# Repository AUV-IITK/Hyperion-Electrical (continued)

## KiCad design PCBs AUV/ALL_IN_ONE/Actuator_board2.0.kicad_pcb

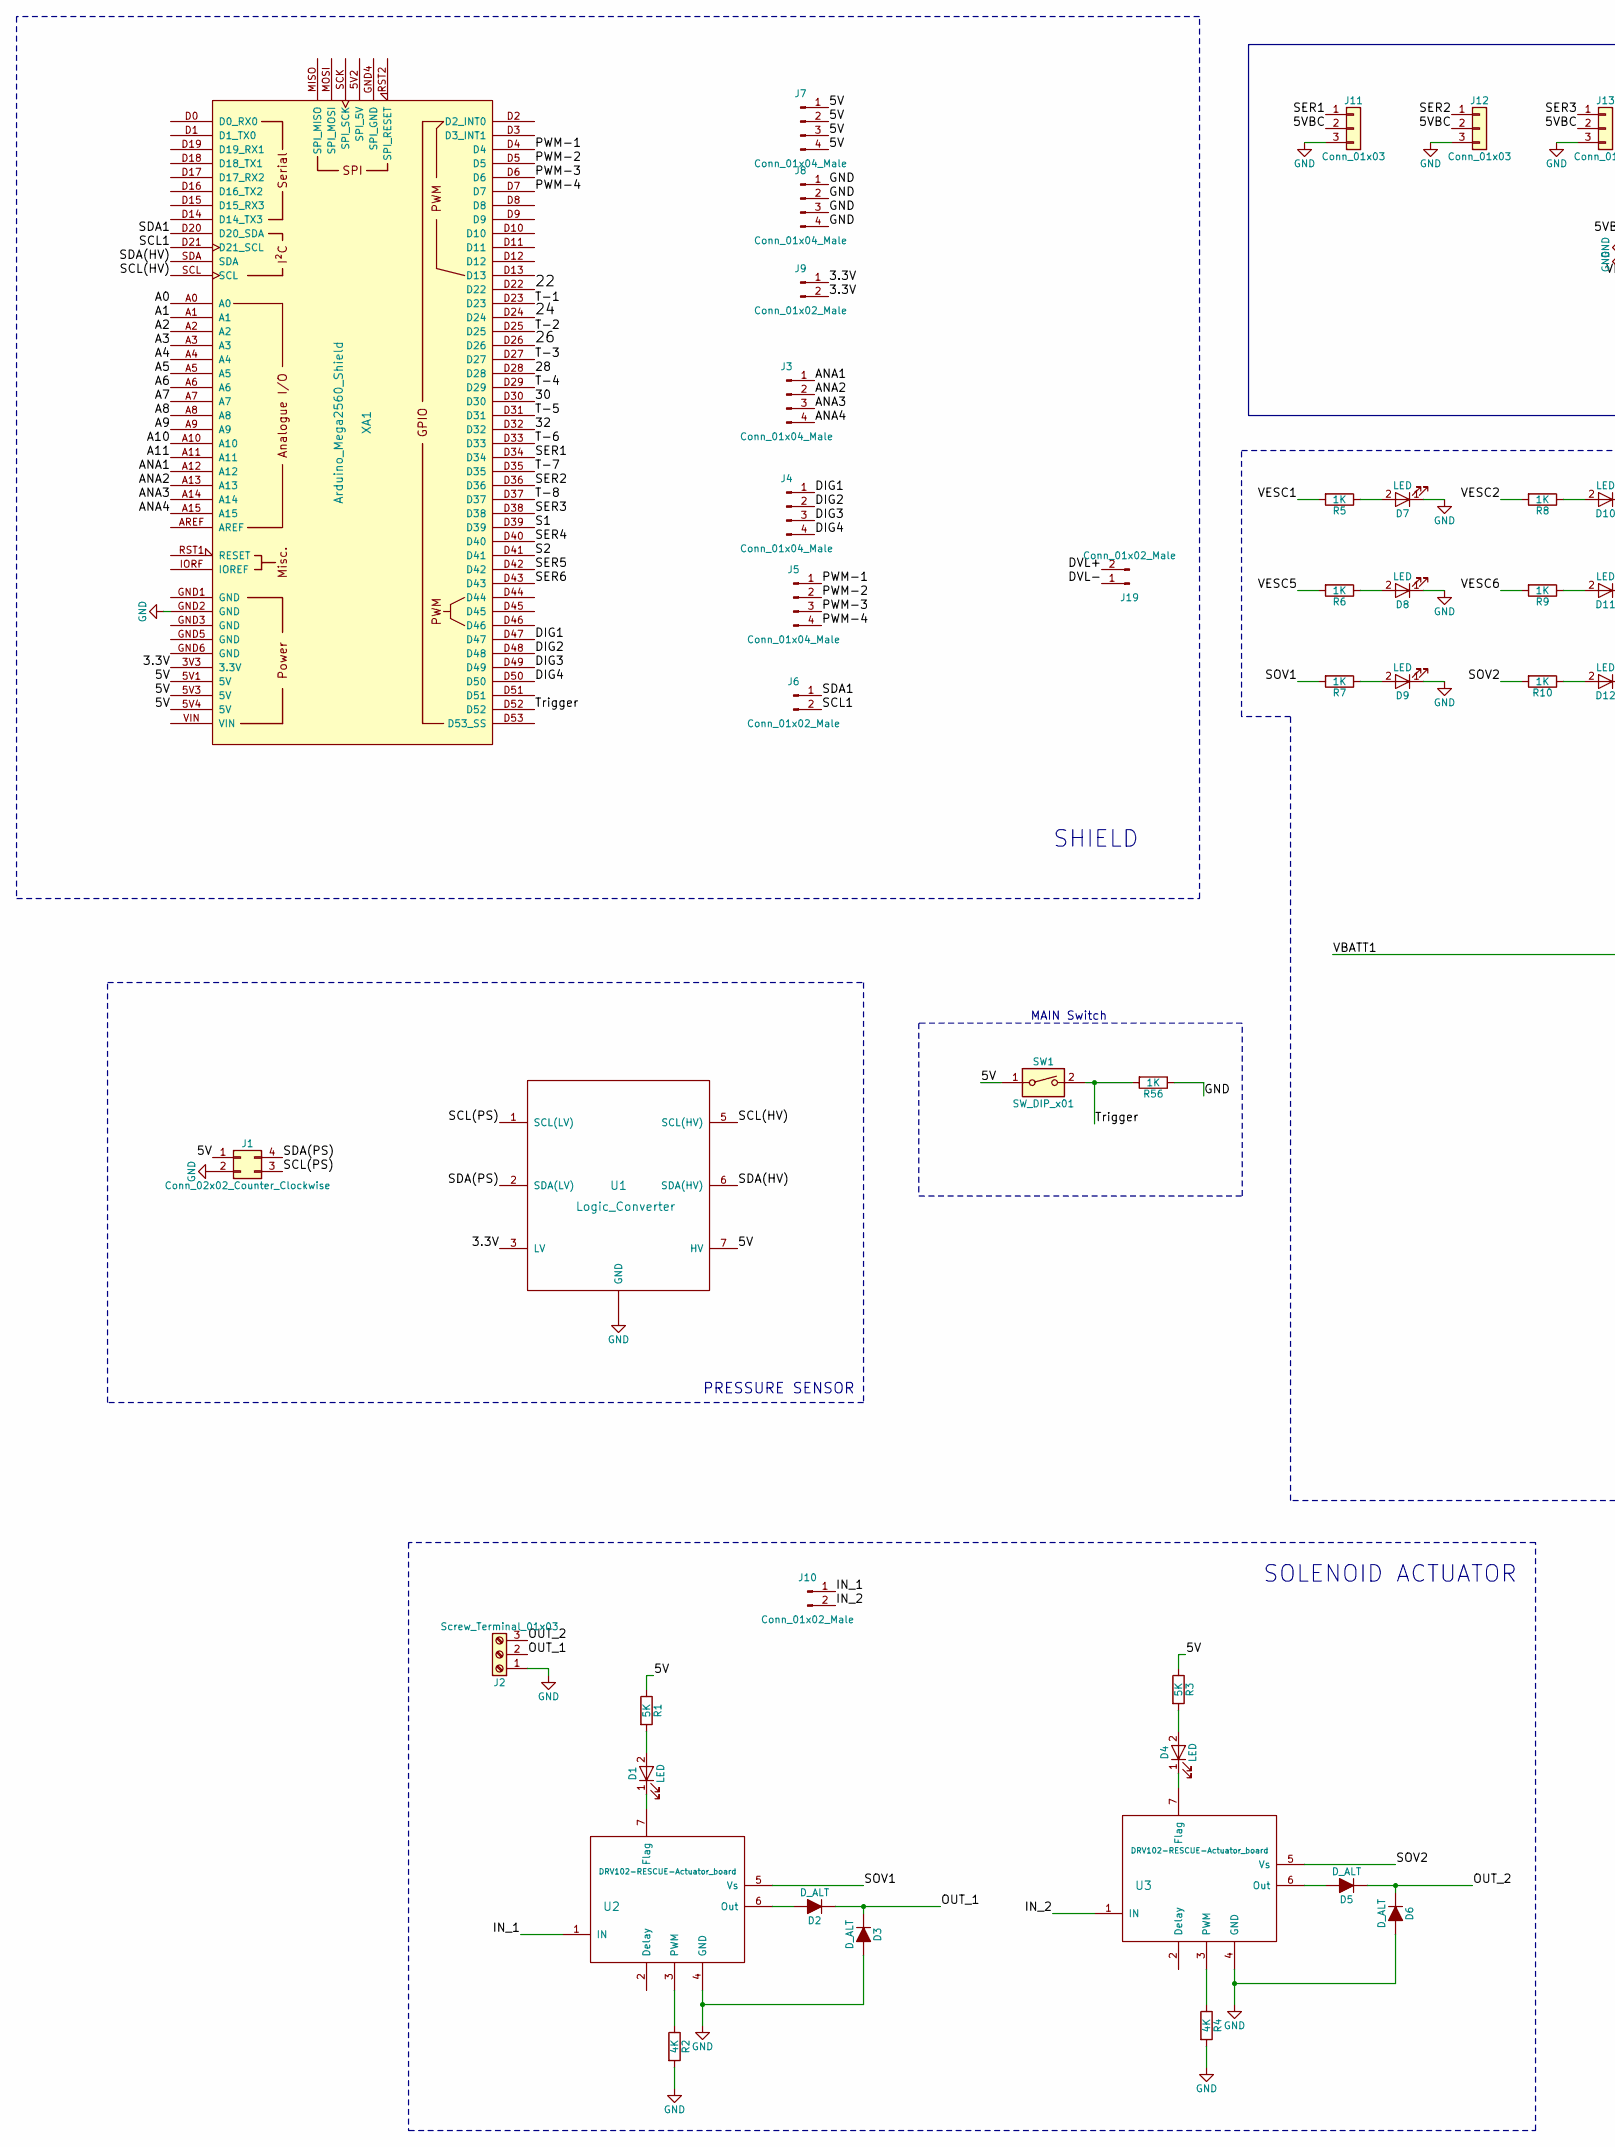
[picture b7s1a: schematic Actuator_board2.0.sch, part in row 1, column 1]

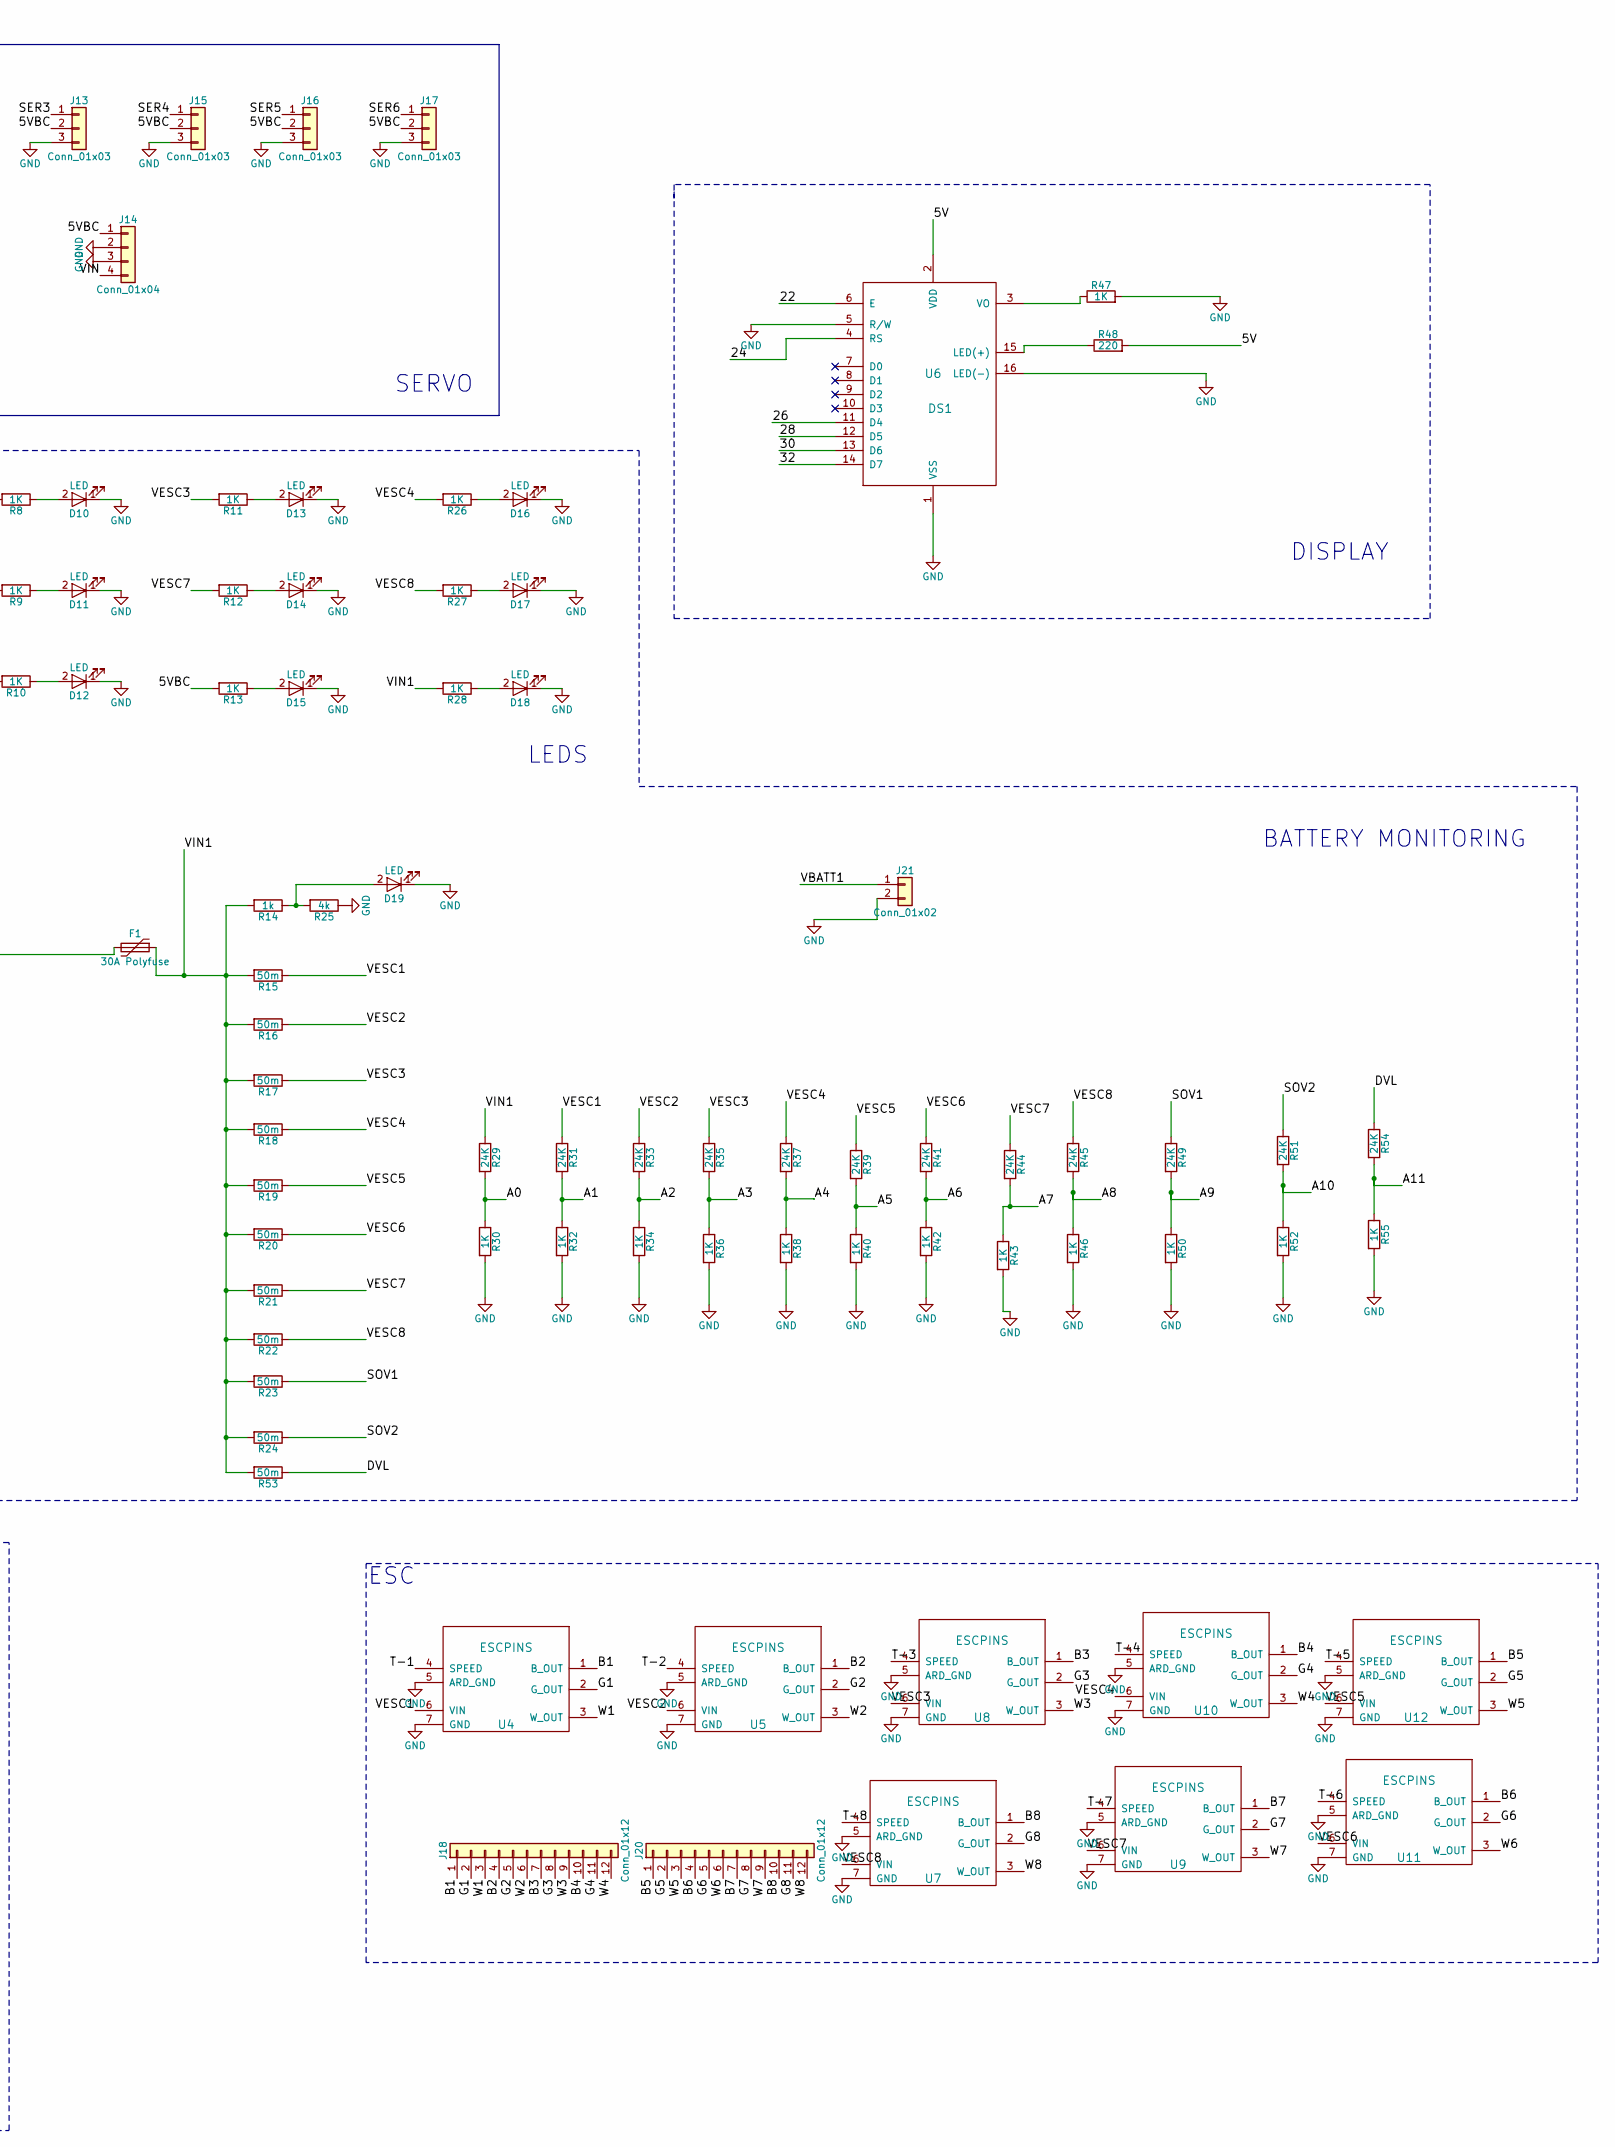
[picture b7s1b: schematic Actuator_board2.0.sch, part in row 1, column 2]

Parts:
D1, D4, D7, D8, D9, D10, D11, D12, D13, D14, D15, D16, D17, D18, D19: LED; LED_D10.0mm
D2, D3, D5, D6: D_ALT; DO-214AB
F1: 30A Polyfuse; Fuse_SMD1206_HandSoldering
J1: Conn_02x02_Counter_Clockwise; Molex_PicoClasp_501331-0407_1x04_P1.0mm_Vertical
J2: Screw_Terminal_01x03; 1_3 pin&socket
J3, J4, J5, J7, J8: Conn_01x04_Male; Molex_PicoClasp_501331-0407_1x04_P1.0mm_Vertical
J6, J9, J10, J19: Conn_01x02_Male; Molex_PicoClasp_501331-0207_1x02_P1.0mm_Vertical
J11, J12, J13, J15, J16, J17: Conn_01x03; TerminalBlock_bornier-3_P5.08mm
J14: Conn_01x04; TerminalBlock_bornier-4_P5.08mm
J18, J20: Conn_01x12; 4_3connector
J21: Conn_01x02; 46817-1002 Guardian 2 Circuit Power Plug000
R1, R3: 5K; R_1206_HandSoldering
R2, R4: 4K; R_1206_HandSoldering
R5, R6, R7, R8, R9, R10, R11, R12, R13, R26, R27, R28, R30, R32, R34, R36, R38, R40, R42, R43, R46, R47, R50, R52, R55, R56: 1K; R_1206_HandSoldering
R14: 1k; R_1206_HandSoldering
R15, R16, R17, R18, R19, R20, R21, R22, R23, R24, R53: 50m; R_1206_HandSoldering
R25: 4k; R_1206_HandSoldering
R29, R31, R33, R35, R37, R39, R41, R44, R45, R49, R51, R54: 24K; R_1206_HandSoldering
R48: 220; R_1206_HandSoldering
SW1: SW_DIP_x01; Molex_PicoClasp_501331-0207_1x02_P1.0mm_Vertical
U1: Logic_Converter; logic_converter
U2, U3: DRV102-RESCUE-Actuator_board; TO-263-7_TabPin4
U4, U5, U7, U8, U9, U10, U11, U12: ESCPINS; esc
U6: DS1; WC1602A
XA1: Arduino_Mega2560_Shield

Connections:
/3.3V: J9.1, J9.2, U1.3 (LV), XA1.3V3 (3.3V)
/5V: J1.1, J7.1, J7.2, J7.3, J7.4, R1.1, R3.1, R48.2, SW1.1, U1.7 (HV), U6.2 (VDD), XA1.5V1 (5V), XA1.5V3 (5V), XA1.5V4 (5V)
/5VBC: J11.2, J12.2, J13.2, J14.1, J15.2, J16.2, J17.2, R13.2
/22: U6.6 (E), XA1.D22
/24: U6.4 (RS), XA1.D24
/26: U6.11 (D4), XA1.D26
/28: U6.12 (D5), XA1.D28
/30: U6.13 (D6), XA1.D30
/32: U6.14 (D7), XA1.D32
/A0: R29.2, R30.1, XA1.A0
/A1: R31.2, R32.1, XA1.A1
/A2: R33.2, R34.1, XA1.A2
/A3: R35.2, R36.1, XA1.A3
/A4: R37.2, R38.1, XA1.A4
/A5: R39.2, R40.1, XA1.A5
/A6: R41.2, R42.1, XA1.A6
/A7: R43.1, R44.2, XA1.A7
/A8: R45.2, R46.1, XA1.A8
/A9: R49.2, R50.1, XA1.A9
/A10: R51.2, R52.1, XA1.A10
/A11: R54.2, R55.1, XA1.A11
/ANA1: J3.1, XA1.A12
/ANA2: J3.2, XA1.A13
/ANA3: J3.3, XA1.A14
/ANA4: J3.4, XA1.A15
/B1: J18.1, U4.1 (B_OUT)
/B2: J18.4, U5.1 (B_OUT)
/B3: J18.7, U8.1 (B_OUT)
/B4: J18.10, U10.1 (B_OUT)
/B5: J20.1, U12.1 (B_OUT)
/B6: J20.4, U11.1 (B_OUT)
/B7: J20.7, U9.1 (B_OUT)
/B8: J20.10, U7.1 (B_OUT)
/DIG1: J4.1, XA1.D47
/DIG2: J4.2, XA1.D48
/DIG3: J4.3, XA1.D49
/DIG4: J4.4, XA1.D50
/DVL: R53.1, R54.1
/DVL+: J19.2
/DVL-: J19.1
/G1: J18.2, U4.2 (G_OUT)
/G2: J18.5, U5.2 (G_OUT)
/G3: J18.8, U8.2 (G_OUT)
/G4: J18.11, U10.2 (G_OUT)
/G5: J20.2, U12.2 (G_OUT)
/G6: J20.5, U11.2 (G_OUT)
/G7: J20.8, U9.2 (G_OUT)
/G8: J20.11, U7.2 (G_OUT)
/IN_1: J10.1, U2.1 (IN)
/IN_2: J10.2, U3.1 (IN)
/OUT_1: D2.1 (K), D3.1 (K), J2.2
/OUT_2: D5.1 (K), D6.1 (K), J2.3
/PWM-1: J5.1, XA1.D4
/PWM-2: J5.2, XA1.D5
/PWM-3: J5.3, XA1.D6
/PWM-4: J5.4, XA1.D7
/S1: XA1.D39
/S2: XA1.D41
/SCL1: J6.2, XA1.D21 (D21_SCL)
/SCL(HV): U1.5 (SCL(HV)), XA1.SCL
/SCL(PS): J1.3, U1.1 (SCL(LV))
/SDA1: J6.1, XA1.D20 (D20_SDA)
/SDA(HV): U1.6 (SDA(HV)), XA1.SDA
/SDA(PS): J1.4, U1.2 (SDA(LV))
/SER1: J11.1, XA1.D34
/SER2: J12.1, XA1.D36
/SER3: J13.1, XA1.D38
/SER4: J15.1, XA1.D40
/SER5: J16.1, XA1.D42
/SER6: J17.1, XA1.D43
/SOV1: R7.2, R23.1, R49.1, U2.5 (Vs)
/SOV2: R10.2, R24.1, R51.1, U3.5 (Vs)
/T-1: U4.4 (SPEED), XA1.D23
/T-2: U5.4 (SPEED), XA1.D25
/T-3: U8.4 (SPEED), XA1.D27
/T-4: U10.4 (SPEED), XA1.D29
/T-5: U12.4 (SPEED), XA1.D31
/T-6: U11.4 (SPEED), XA1.D33
/T-7: U9.4 (SPEED), XA1.D35
/T-8: U7.4 (SPEED), XA1.D37
/VBATT1: F1.2, J21.1
/VESC1: R5.2, R15.1, R31.1, U4.6 (VIN)
/VESC2: R8.2, R16.1, R33.1, U5.6 (VIN)
/VESC3: R11.2, R17.1, R35.1, U8.6 (VIN)
/VESC4: R18.1, R26.2, R37.1, U10.6 (VIN)
/VESC5: R6.2, R19.1, R39.1, U12.6 (VIN)
/VESC6: R9.2, R20.1, R41.1, U11.6 (VIN)
/VESC7: R12.2, R21.1, R44.1, U9.6 (VIN)
/VESC8: R22.1, R27.2, R45.1, U7.6 (VIN)
/VIN: J14.4
/VIN1: F1.1, R14.2, R15.2, R16.2, R17.2, R18.2, R19.2, R20.2, R21.2, R22.2, R23.2, R24.2, R28.2, R29.1, R53.2
/W1: J18.3, U4.3 (W_OUT)
/W2: J18.6, U5.3 (W_OUT)
/W3: J18.9, U8.3 (W_OUT)
/W4: J18.12, U10.3 (W_OUT)
/W5: J20.3, U12.3 (W_OUT)
/W6: J20.6, U11.3 (W_OUT)
/W7: J20.9, U9.3 (W_OUT)
/W8: J20.12, U7.3 (W_OUT)
GND: D3.2 (A), D6.2 (A), D7.1 (K), D8.1 (K), D9.1 (K), D10.1 (K), D11.1 (K), D12.1 (K), D13.1 (K), D14.1 (K), D15.1 (K), D16.1 (K), D17.1 (K), D18.1 (K), D19.1 (K), J1.2, J2.1, J8.1, J8.2, J8.3, J8.4, J11.3, J12.3, J13.3, J14.2, J14.3, J15.3, J16.3, J17.3, J21.2, R2.2, R4.2, R25.1, R30.2, R32.2, R34.2, R36.2, R38.2, R40.2, R42.2, R43.2, R46.2, R47.2, R50.2, R52.2, R55.2, R56.1, U1.~ (GND), U2.4 (GND), U3.4 (GND), U4.5 (ARD_GND), U4.7 (GND), U5.5 (ARD_GND), U5.7 (GND), U6.1 (VSS), U6.5 (R/W), U6.16 (LED(-)), U7.5 (ARD_GND), U7.7 (GND), U8.5 (ARD_GND), U8.7 (GND), U9.5 (ARD_GND), U9.7 (GND), U10.5 (ARD_GND), U10.7 (GND), U11.5 (ARD_GND), U11.7 (GND), U12.5 (ARD_GND), U12.7 (GND), XA1.GND2 (GND)
unnamed: D1.1 (K), U2.7 (Flag)
unnamed: D1.2 (A), R1.2
unnamed: D2.2 (A), U2.6 (Out)
unnamed: D4.1 (K), U3.7 (Flag)
unnamed: D4.2 (A), R3.2
unnamed: D5.2 (A), U3.6 (Out)
unnamed: D7.2 (A), R5.1
unnamed: D8.2 (A), R6.1
unnamed: D9.2 (A), R7.1
unnamed: D10.2 (A), R8.1
unnamed: D11.2 (A), R9.1
unnamed: D12.2 (A), R10.1
unnamed: D13.2 (A), R11.1
unnamed: D14.2 (A), R12.1
unnamed: D15.2 (A), R13.1
unnamed: D16.2 (A), R26.1
unnamed: D17.2 (A), R27.1
unnamed: D18.2 (A), R28.1
unnamed: D19.2 (A), R14.1, R25.2
unnamed: R2.1, U2.3 (PWM)
unnamed: R4.1, U3.3 (PWM)
unnamed: R47.1, U6.3 (VO)
unnamed: R48.1, U6.15 (LED(+))
unnamed: R56.2, SW1.2, XA1.D52

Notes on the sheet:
ESC
DISPLAY
BATTERY MONITORING
SOLENOID ACTUATOR
SHIELD
PRESSURE SENSOR
SERVO
LEDS
MAIN Switch

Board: 2 copper layers, 109 parts (4 on the bottom side), 118 nets, no tracks yet.

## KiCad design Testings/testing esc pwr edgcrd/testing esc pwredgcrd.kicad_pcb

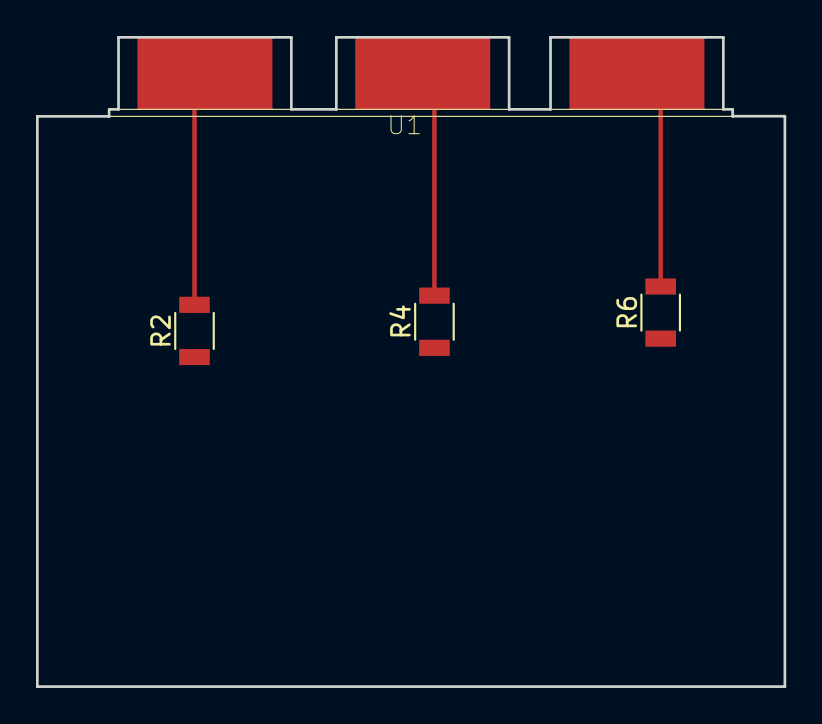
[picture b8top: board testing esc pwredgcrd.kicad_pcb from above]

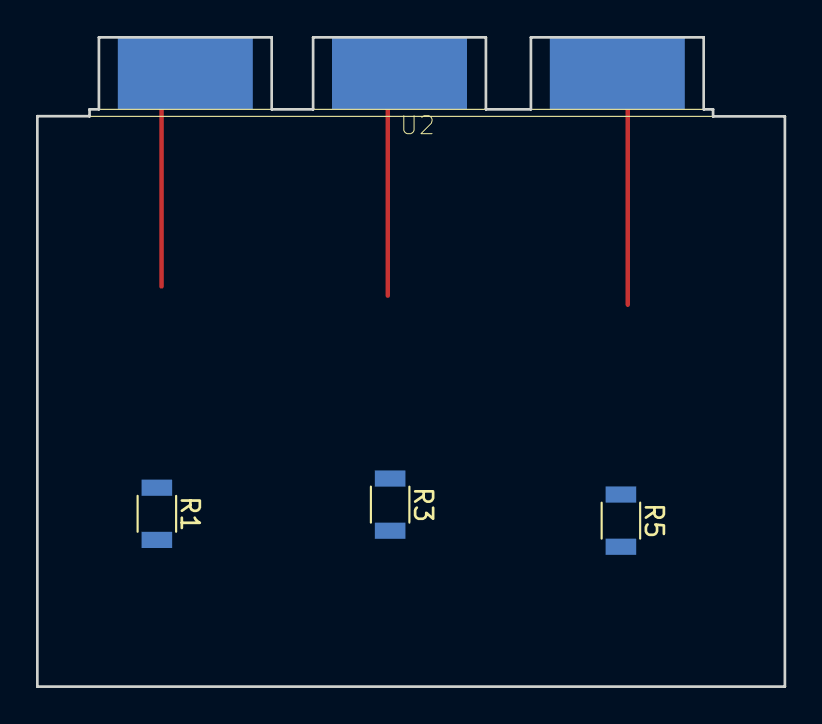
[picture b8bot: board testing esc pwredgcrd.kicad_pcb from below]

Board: 2 copper layers, 41.5 x 36.1 mm, 8 parts (4 on the bottom side), 3 nets.

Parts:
R1, R2, R3, R4, R5, R6: R; R_1206
U1: 3pin; esc_power_redefined_3pin
U2: 3pin; esc_power_redined_mirror_3pin

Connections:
unnamed: R2.2, U1.1
unnamed: R4.2, U1.2
unnamed: R6.2, U1.3

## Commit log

2019-06-28 pcb_updates
2020-01-12 upgrading_repo
2020-05-09 Adding Anahita,Kill_Switch PCBs
